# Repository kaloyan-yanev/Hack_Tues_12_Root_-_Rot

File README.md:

# Hack_Tues_12_Root_-_Rot

Root&Rot e aвтоматизиран smart компостер, който позволява на големи магазини и ресторанти да рециклират техните хранителни остатъци, непродадена или с изтекъл срок на годност хранителна стока и остатъчен опаковачен материал, като ги компостират в натурална тор.

## Какво прави

- Компостер контролиран от ESP
- Засича температура,влажност,Метан и Въглероден Диоксид
- .NET backend server 
- React уебсайт визуализирайки сензорните данн

## Главна Идея

Компостерите са или просто контейнери които фермерите си подържат или индустриални, които не могат да бъдат използвани от ресторанти и Супермаркети. Root&Rot цели да поволи и на ресторантите и супермаркетите да си рециклират храната, която иначе щеше да изхвърля

## Поток на данни 

1. Root&Rot действа като компостер и събира данните
2. използва се python скрипт, за да се изпрати тази информация да MariaDB
3. От сайта се въвежда дали е изхвърляно месо или млечни продукти
4. Пращат се извънредни команди ако има нужда от сайта до esp
5. Следи се процеса на компостиране и се показва на сайта отделно за всеки компостер добаве

## Защо има значение

- рециклираме иначе продукти които ще се изхвърлят
- нямаляване на вредните емисии, които се създават от гниенето на продукти
- позволява на компании, които досега не са имали комспотери - да имат
- печелене на пари от продаването на тор като им даваме част от печалбата

## Прототип

## Hardware

- ESP 32
- мотор
- 2 сензора за температура
- 1 сензор за Метан
- 1 сензор за Въглероден Диоксид
- 1 сензор за влага
- 1 сензор за Дебит

## Stack

## Равитие в бъдещето

-Root&Rot ще се използва във всеки магазин и ресторант, за да рециклира продукти
- по-добри компоненти за сигурна работа
- по-прецизни сметки за прогреса на тор
- по-ефективно от прототип
- достатъчно умно и лесно инсталиране за минимални разходи на ток и минимални нужни знания
- мобилно приложение

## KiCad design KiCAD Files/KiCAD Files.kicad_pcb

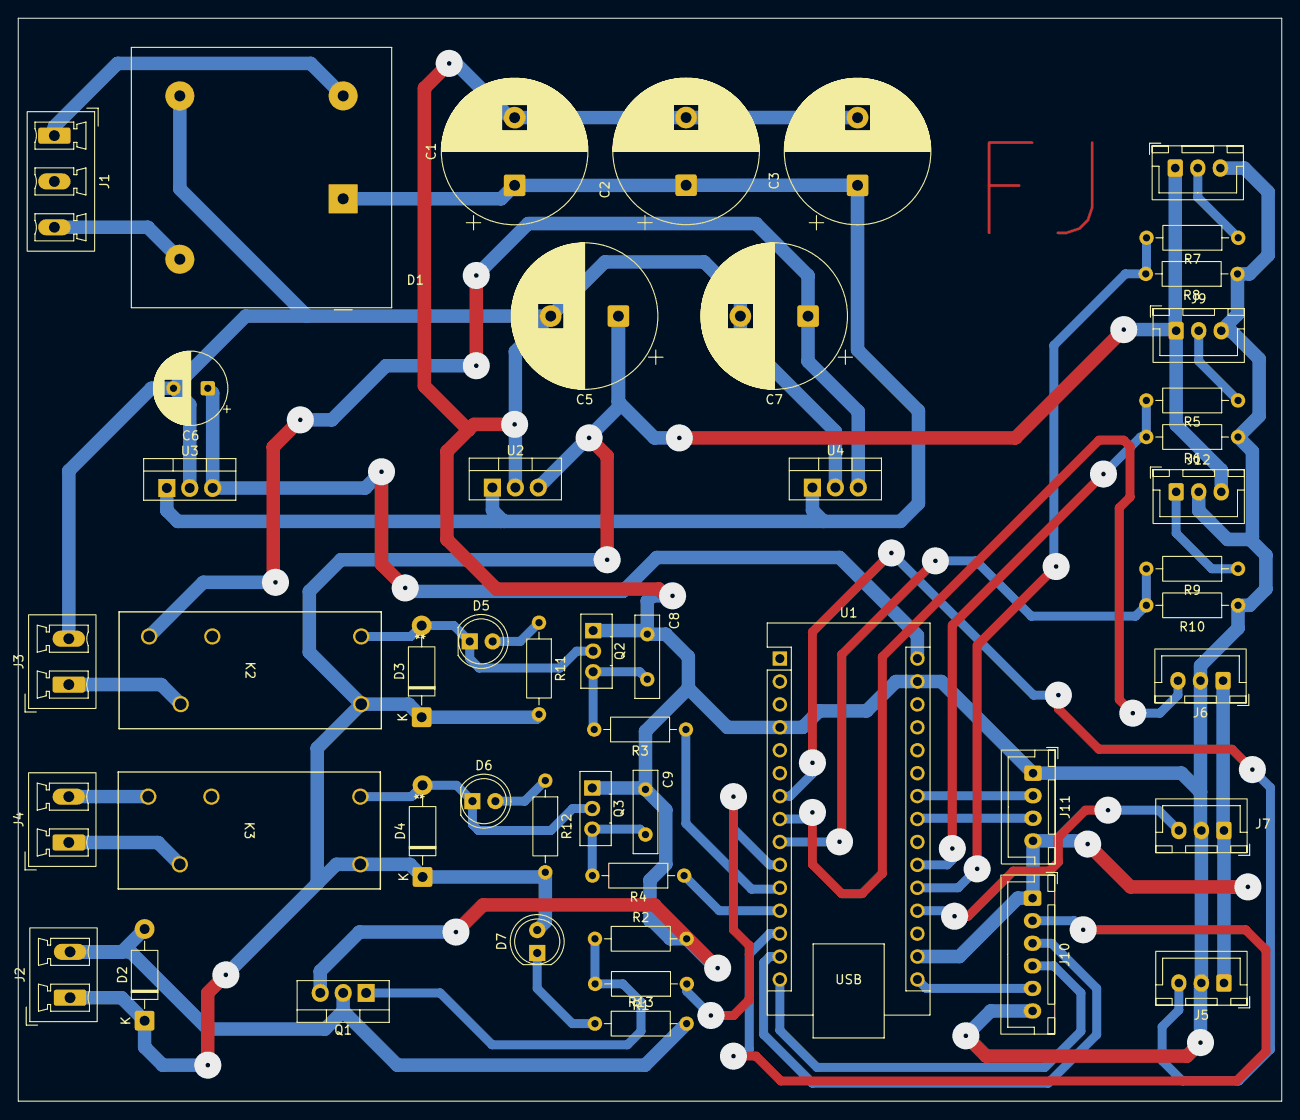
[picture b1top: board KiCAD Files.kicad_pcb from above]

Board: 2 copper layers, 140.0 x 120.0 mm, 49 parts (0 on the bottom side), 38 nets.

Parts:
C1, C2, C3, C5, C7: 4700uF; CP_Radial_D16.0mm_P7.50mm
C6: 100uF; CP_Radial_D8.0mm_P3.80mm
C8, C9: 100nF; C_Disc_D9.0mm_W2.5mm_P5.00mm
D1: KBPC3510W; Diode_Bridge_GeneSiC_KBPC_W
D2, D3, D4: 1N4007; D_DO-41_SOD81_P10.16mm_Horizontal
D5, D6, D7: LED; LED_D5.0mm
J1: Power-Input; PhoenixContact_MCV_1,5_3-G-5.08_1x03_P5.08mm_Vertical
J2: Pump-Conn; PhoenixContact_MCV_1,5_2-G-5.08_1x02_P5.08mm_Vertical
J3: Chopper-Conn; PhoenixContact_MCV_1,5_2-G-5.08_1x02_P5.08mm_Vertical
J4: Heater-Conn; PhoenixContact_MCV_1,5_2-G-5.08_1x02_P5.08mm_Vertical
J5: Term-1; JST_XH_B3B-XH-A_1x03_P2.50mm_Vertical
J6: Term-2; JST_XH_B3B-XH-A_1x03_P2.50mm_Vertical
J7: Humidity; JST_XH_B3B-XH-A_1x03_P2.50mm_Vertical
J8: MQ-2-Methane; JST_XH_B3B-XH-A_1x03_P2.50mm_Vertical
J9: MQ-135-CO2; JST_XH_B3B-XH-A_1x03_P2.50mm_Vertical
J10: SPI-Expansion; JST_XH_B6B-XH-A_1x06_P2.50mm_Vertical
J11: I2C-Expansion; JST_XH_B4B-XH-A_1x04_P2.50mm_Vertical
J12: Flow; JST_XH_B3B-XH-A_1x03_P2.50mm_Vertical
K2: Chopper-Relay; RELAY_G2R-1 AC12_OMR
K3: Heater-Relay; RELAY_G2R-1 AC12_OMR
Q1: IRFZ44N; TO-220-3_Vertical
Q2, Q3: BD139; TO-126-3_Vertical
R1, R11, R12, R13: 100; R_Axial_DIN0207_L6.3mm_D2.5mm_P10.16mm_Horizontal
R2, R5, R7, R9: 10K; R_Axial_DIN0207_L6.3mm_D2.5mm_P10.16mm_Horizontal
R3, R4: 220; R_Axial_DIN0207_L6.3mm_D2.5mm_P10.16mm_Horizontal
R6, R8, R10: 20K; R_Axial_DIN0207_L6.3mm_D2.5mm_P10.16mm_Horizontal
U1: Arduino_Nano_ESP32; Arduino_Nano
U2: LM7805; TO-220-3_Vertical
U3: LM7808; TO-220-3_Vertical
U4: LM7812; TO-220-3_Vertical

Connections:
+3.3V: J5.1, J6.1, J7.1, J10.1, J11.4, U1.17 (3V3)
+5V: C5.1, D2.1 (K), D3.1 (K), D4.1 (K), D7.2 (A), J2.1, J8.1, J9.1, J12.3, K2.5, K3.5, R11.2, R12.2, U2.3 (VO)
+8V: C6.1, U1.30 (VIN), U3.3 (VO)
+12V: C7.1, K2.3, U4.3 (VO)
/CO2: R5.2, R6.2, U1.21 (A2)
/Chopper: R3.1, U1.11 (D8)
/Flow: R9.2, R10.2, U1.9 (D6)
/Heater: R4.1, U1.12 (D9)
/Humidity: J7.3, U1.19 (A0)
/Methane: R7.2, R8.2, U1.20 (A1)
/Pump: R1.1, U1.10 (D7)
/Term-1: J5.3, U1.7 (D4)
/Term-2: J6.3, U1.8 (D5)
GND: C1.2, C2.2, C3.2, C5.2, C6.2, C7.2, C8.2, C9.2, D1.3 (-), J3.2, J5.2, J6.2, J7.2, J8.3, J9.3, J10.6, J11.1, J12.2, Q1.3 (S), Q2.1 (E), Q3.1 (E), R2.2, R6.1, R8.1, R10.1, U1.4 (GND), U1.29 (GND), U2.2 (GND), U3.2 (GND), U4.2 (GND)
unnamed: D2.2 (A), J2.2, Q1.2 (D), R13.2
unnamed: D3.2 (A), D5.1 (K), K2.1, Q2.2 (C)
unnamed: D4.2 (A), D6.1 (K), K3.1, Q3.2 (C)
unnamed: D5.2 (A), R11.1
unnamed: D6.2 (A), R12.1
unnamed: D7.1 (K), R13.1
unnamed: D1.4, J1.1
unnamed: D1.2, J1.3
unnamed: J3.1, K2.4
unnamed: J4.1, K3.4
unnamed: J4.2, K3.3
unnamed: J8.2, R7.1
unnamed: J9.2, R5.1
unnamed: J10.2, U1.13 (D10/CS)
unnamed: J10.3, U1.14 (D11/COPI)
unnamed: J10.4, U1.15 (D12/CIPO)
unnamed: J10.5, U1.16 (D13/SCK)
unnamed: J11.2, U1.24 (SCL/A5)
unnamed: J11.3, U1.23 (SDA/A4)
unnamed: J12.1, R9.1
unnamed: Q1.1 (G), R1.2, R2.1
unnamed: C8.1, Q2.3 (B), R3.2
unnamed: C9.1, Q3.3 (B), R4.2
VS: C1.1, C2.1, C3.1, D1.1 (+), U2.1 (VI), U3.1 (VI), U4.1 (VI)

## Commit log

2026-03-26 Created KiCAD Project
2026-03-26 Fixed folders
2026-03-26 Added the SQL query for database creation
2026-03-26 initial webapp structure with needed folders for organization
2026-03-26 Scaffolded the database succesfully
2026-03-26 started adding controllers and services but committing so that we can clone the branch
2026-03-26 WiFi connection established
2026-03-26 refactored most of the services and continued with ComposterService still need to look at .NET Indentity
2026-03-26 Schematic-V1
2026-03-26 left to do Core Identity and JWT token generation
2026-03-26 Added pages and routing
2026-03-26 Schematic-V2-Add-Flow-Control
2026-03-26 Schemati-Rearranged
2026-03-26 Schematic-Footprints+LEDs
2026-03-26 Layout-Designed
2026-03-26 Added a NavBar to the main page, made the login and signup look far better
2026-03-26 Manually-Routed-V1
2026-03-26 mqtt communication established
2026-03-26 Finalized-2-Layer
2026-03-26 Single-Layer-PCB
2026-03-26 Single-Layer-Big-Pads
2026-03-26 Added-Shielding
2026-03-26 Added-Thermal-Releaves
2026-03-26 Backend should be done only fronend fetches are left
2026-03-26 Finished the architecture for the script for receiving data from the esp32 trough mqtt
2026-03-26 added abstract functions for getting sensor information and controlling actuators
2026-03-26 mqtt sends json sensor information. We are testing with dummy functions for the sensors
2026-03-27 Changed the code to accommodate for the actual format of the json message that is going to be sent
2026-03-27 fetches need to be done still testing endpoints
2026-03-27 Installed IdentityModel.Tokens package and let Rider make it's changes
2026-03-27 Fixed wrong row name in query
2026-03-27 added methane levels monitoring and adaptable stirring(If there is methane the compost needs oxygen and oxygen is supplied by stirring it)
2026-03-27 wil delete some folders so commiting before that
    will use version control if needed
2026-03-27 Wrote scripts for sending stir signal and temperature threshold value
2026-03-27 fixed the problems with cache files and edited the database
2026-03-27 Removed unncessary files
2026-03-27 Autherization working tested with postman Scripts left and database manipulation
2026-03-27 patched up an error with StirTor
2026-03-27 Finished the architecture for the script for receiving data from the esp32 trough mqtt
    Merged my changes, which consist of adding the python scripts and configuring gitignore
2026-03-27 Added the python scripts to Server Solution and updated gitignore to ignore files changed by IDE
2026-03-27 added the missing slnx file
2026-03-27 fixed backend will connect fronend to backend
2026-03-27 FIxing git
2026-03-27 fixed frontend
2026-03-27 added Cors and policy
2026-03-27 Fighting with fetches
2026-03-27 fixed json conversion on frontend
2026-03-27 EVERYTHING IN THE FRONT END WORKS
2026-03-27 added code for python scripts
2026-03-27 completed code with sensor and actuator logic that runs on esp32 s3 dev board
2026-03-27 rewrited relay logic to work active low
2026-03-27 Created a new database for storing composter data history
2026-03-27 Added bools in database and made the DbContext accurate
2026-03-27 have the same problem as 12 hours ago but forgot how to fix it we now run the file with dotnet run
2026-03-28 Added emoji buttons
2026-03-28 Got algorithm to check progress
2026-03-28 working on the emoji buttons
2026-03-28 Fixed errors
2026-03-28 Code tested with hardware and everything is working
2026-03-28 finally working icons and python script execution
2026-03-28 Redesigned&Fixed-Final-PCB
2026-03-28 Code with demonstration purposes
2026-03-28 presentation
2026-03-28 Final push
2026-03-28 rot was doubled
2026-03-28 final commit
2026-04-02 testing if i can push
2026-04-23 Final changes to the server and client of the webapp
    done by Georgi15
